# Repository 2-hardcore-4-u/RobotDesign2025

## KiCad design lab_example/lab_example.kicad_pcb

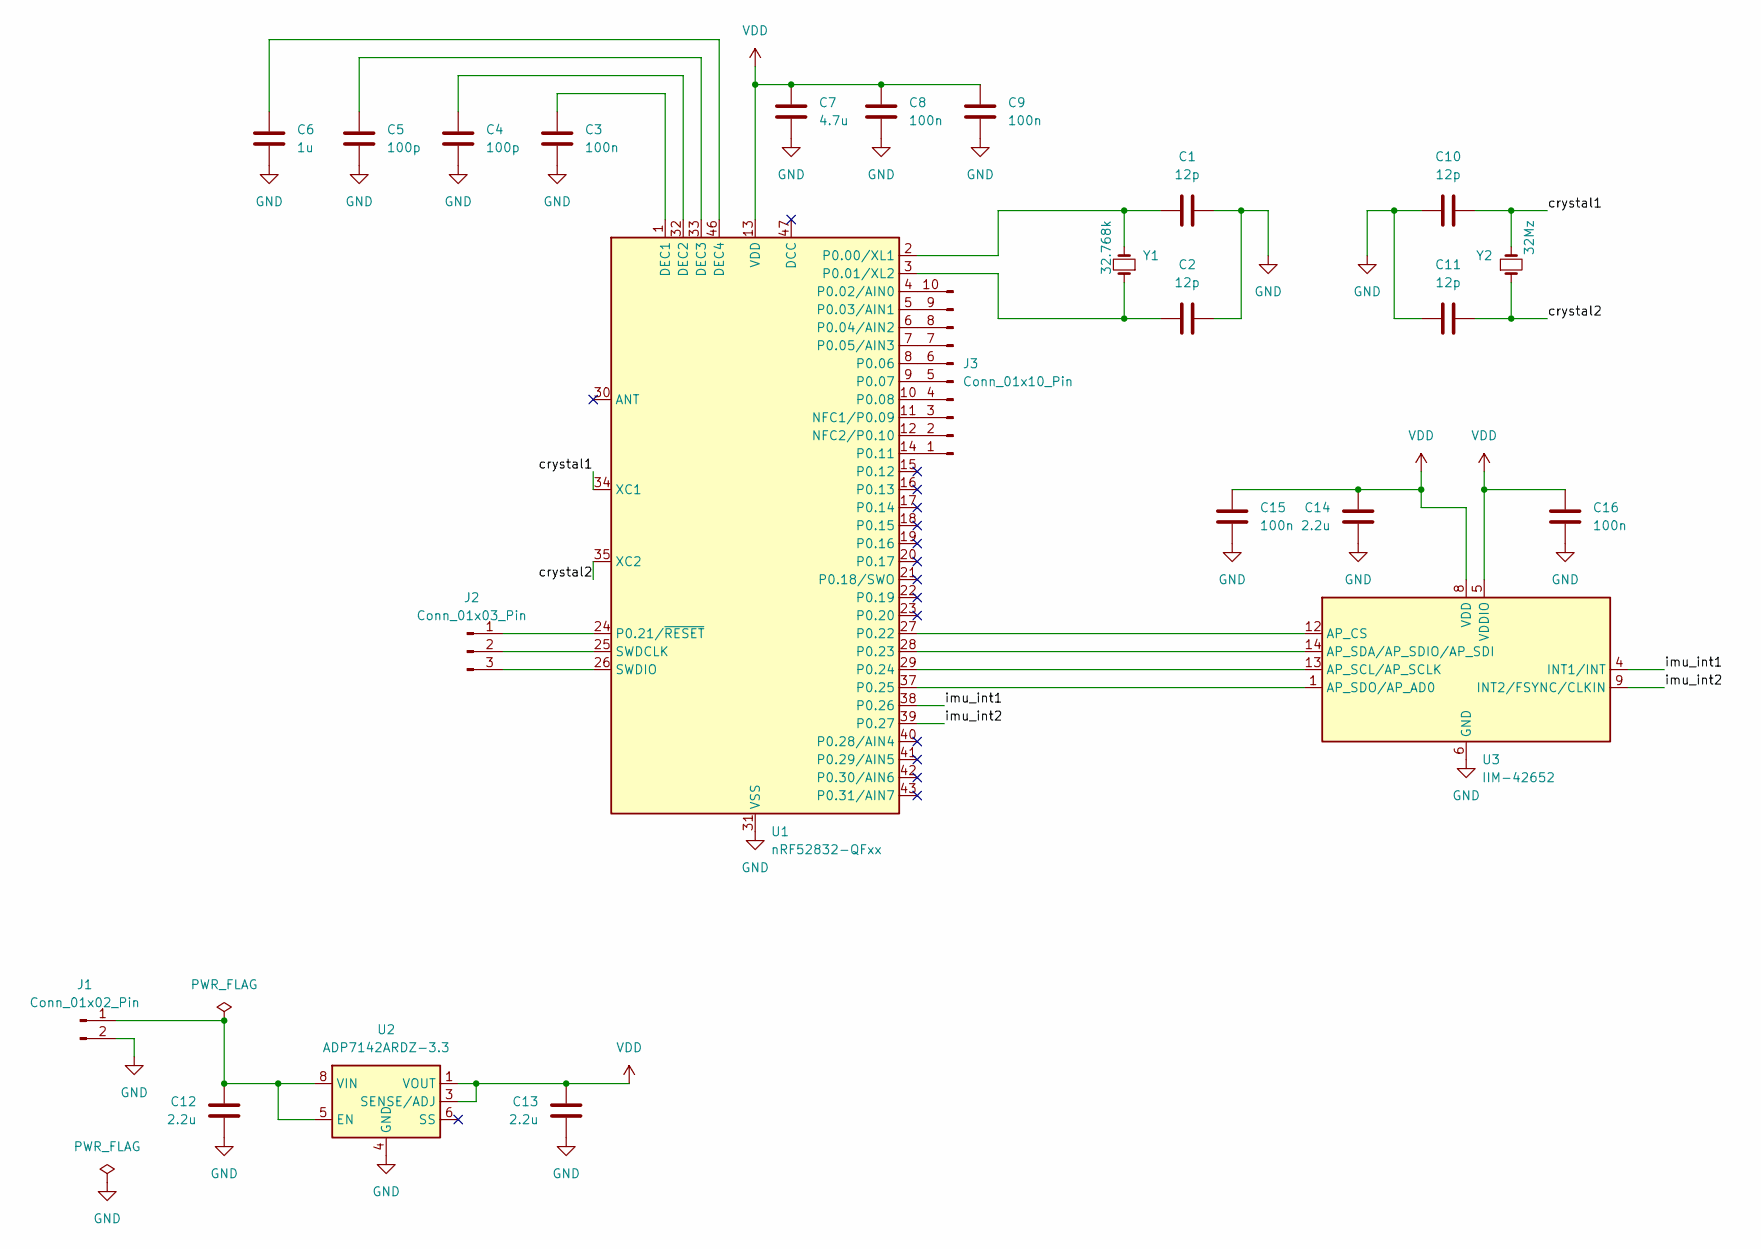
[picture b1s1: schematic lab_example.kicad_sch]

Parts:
C1, C2, C10, C11: 12p; C_0805_2012Metric
C3, C8, C9, C15, C16: 100n; C_0805_2012Metric
C4, C5: 100p; C_0805_2012Metric
C6: 1u; C_0805_2012Metric
C7: 4.7u; C_0805_2012Metric
C12, C13, C14: 2.2u; C_0805_2012Metric
J1: Conn_01x02_Pin; PinHeader_1x02_P2.54mm_Horizontal
J2: Conn_01x03_Pin; PinHeader_1x03_P2.54mm_Horizontal
J3: Conn_01x10_Pin; PinHeader_1x10_P2.54mm_Vertical
U1: nRF52832-QFxx; QFN-48-1EP_6x6mm_P0.4mm_EP4.6x4.6mm
U2: ADP7142ARDZ-3.3; SOIC-8-1EP_3.9x4.9mm_P1.27mm_EP2.29x3mm
U3: IIM-42652; Bosch_LGA-14_3x2.5mm_P0.5mm
Y1: 32.768k; Crystal_SMD_2012-2Pin_2.0x1.2mm_HandSoldering
Y2: 32Mz; Crystal_SMD_2012-2Pin_2.0x1.2mm_HandSoldering

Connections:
/crystal1: C10.1, U1.34 (XC1), Y2.2
/crystal2: C11.2, U1.35 (XC2), Y2.1
/imu_int1: U1.38 (P0.26), U3.4 (INT1/INT)
/imu_int2: U1.39 (P0.27), U3.9 (INT2/FSYNC/CLKIN)
GND: C1.2, C2.1, C3.2, C4.2, C5.2, C6.2, C7.2, C8.2, C9.2, C10.2, C11.1, C12.1, C13.1, C14.1, C15.2, C16.2, J1.2, U1.31 (VSS), U1.45 (VSS), U1.49 (VSS), U2.4 (GND), U2.9 (GND), U3.6 (GND), U3.7 (GND)
unnamed: C12.2, J1.1, U2.5 (EN), U2.7 (VIN), U2.8 (VIN)
unnamed: J2.1, U1.24 (P0.21/~RESET)
unnamed: J2.2, U1.25 (SWDCLK)
unnamed: J2.3, U1.26 (SWDIO)
unnamed: J3.1, U1.14 (P0.11)
unnamed: J3.2, U1.12 (NFC2/P0.10)
unnamed: J3.3, U1.11 (NFC1/P0.09)
unnamed: J3.4, U1.10 (P0.08)
unnamed: J3.5, U1.9 (P0.07)
unnamed: J3.6, U1.8 (P0.06)
unnamed: J3.7, U1.7 (P0.05/AIN3)
unnamed: J3.8, U1.6 (P0.04/AIN2)
unnamed: J3.9, U1.5 (P0.03/AIN1)
unnamed: J3.10, U1.4 (P0.02/AIN0)
unnamed: C3.1, U1.1 (DEC1)
unnamed: C4.1, U1.32 (DEC2)
unnamed: C5.1, U1.33 (DEC3)
unnamed: C6.1, U1.46 (DEC4)
unnamed: C1.1, U1.2 (P0.00/XL1), Y1.2
unnamed: C2.2, U1.3 (P0.01/XL2), Y1.1
unnamed: U1.27 (P0.22), U3.12 (AP_CS)
unnamed: U1.28 (P0.23), U3.14 (AP_SDA/AP_SDIO/AP_SDI)
unnamed: U1.29 (P0.24), U3.13 (AP_SCL/AP_SCLK)
unnamed: U1.37 (P0.25), U3.1 (AP_SDO/AP_AD0)
VDD: C7.1, C8.1, C9.1, C13.2, C14.2, C15.1, C16.1, U1.13 (VDD), U1.36 (VDD), U1.48 (VDD), U2.1 (VOUT), U2.2 (VOUT), U2.3 (SENSE/ADJ), U3.5 (VDDIO), U3.8 (VDD)

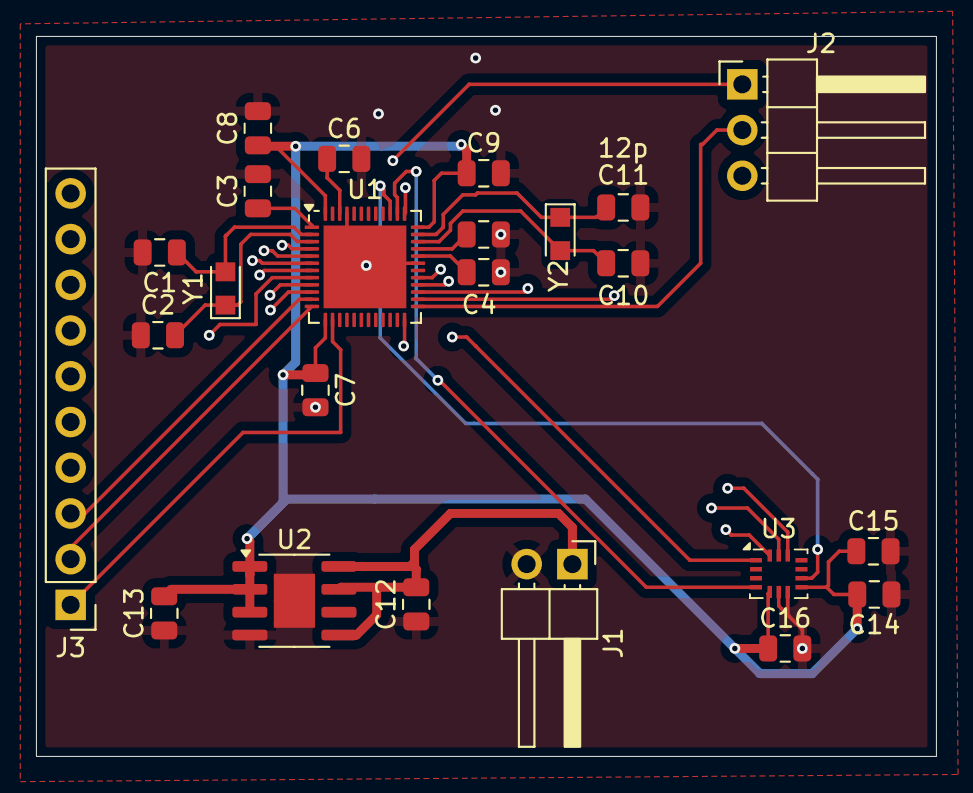
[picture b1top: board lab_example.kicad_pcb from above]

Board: 4 copper layers, 50.0 x 40.0 mm, 24 parts (0 on the bottom side), 30 nets.

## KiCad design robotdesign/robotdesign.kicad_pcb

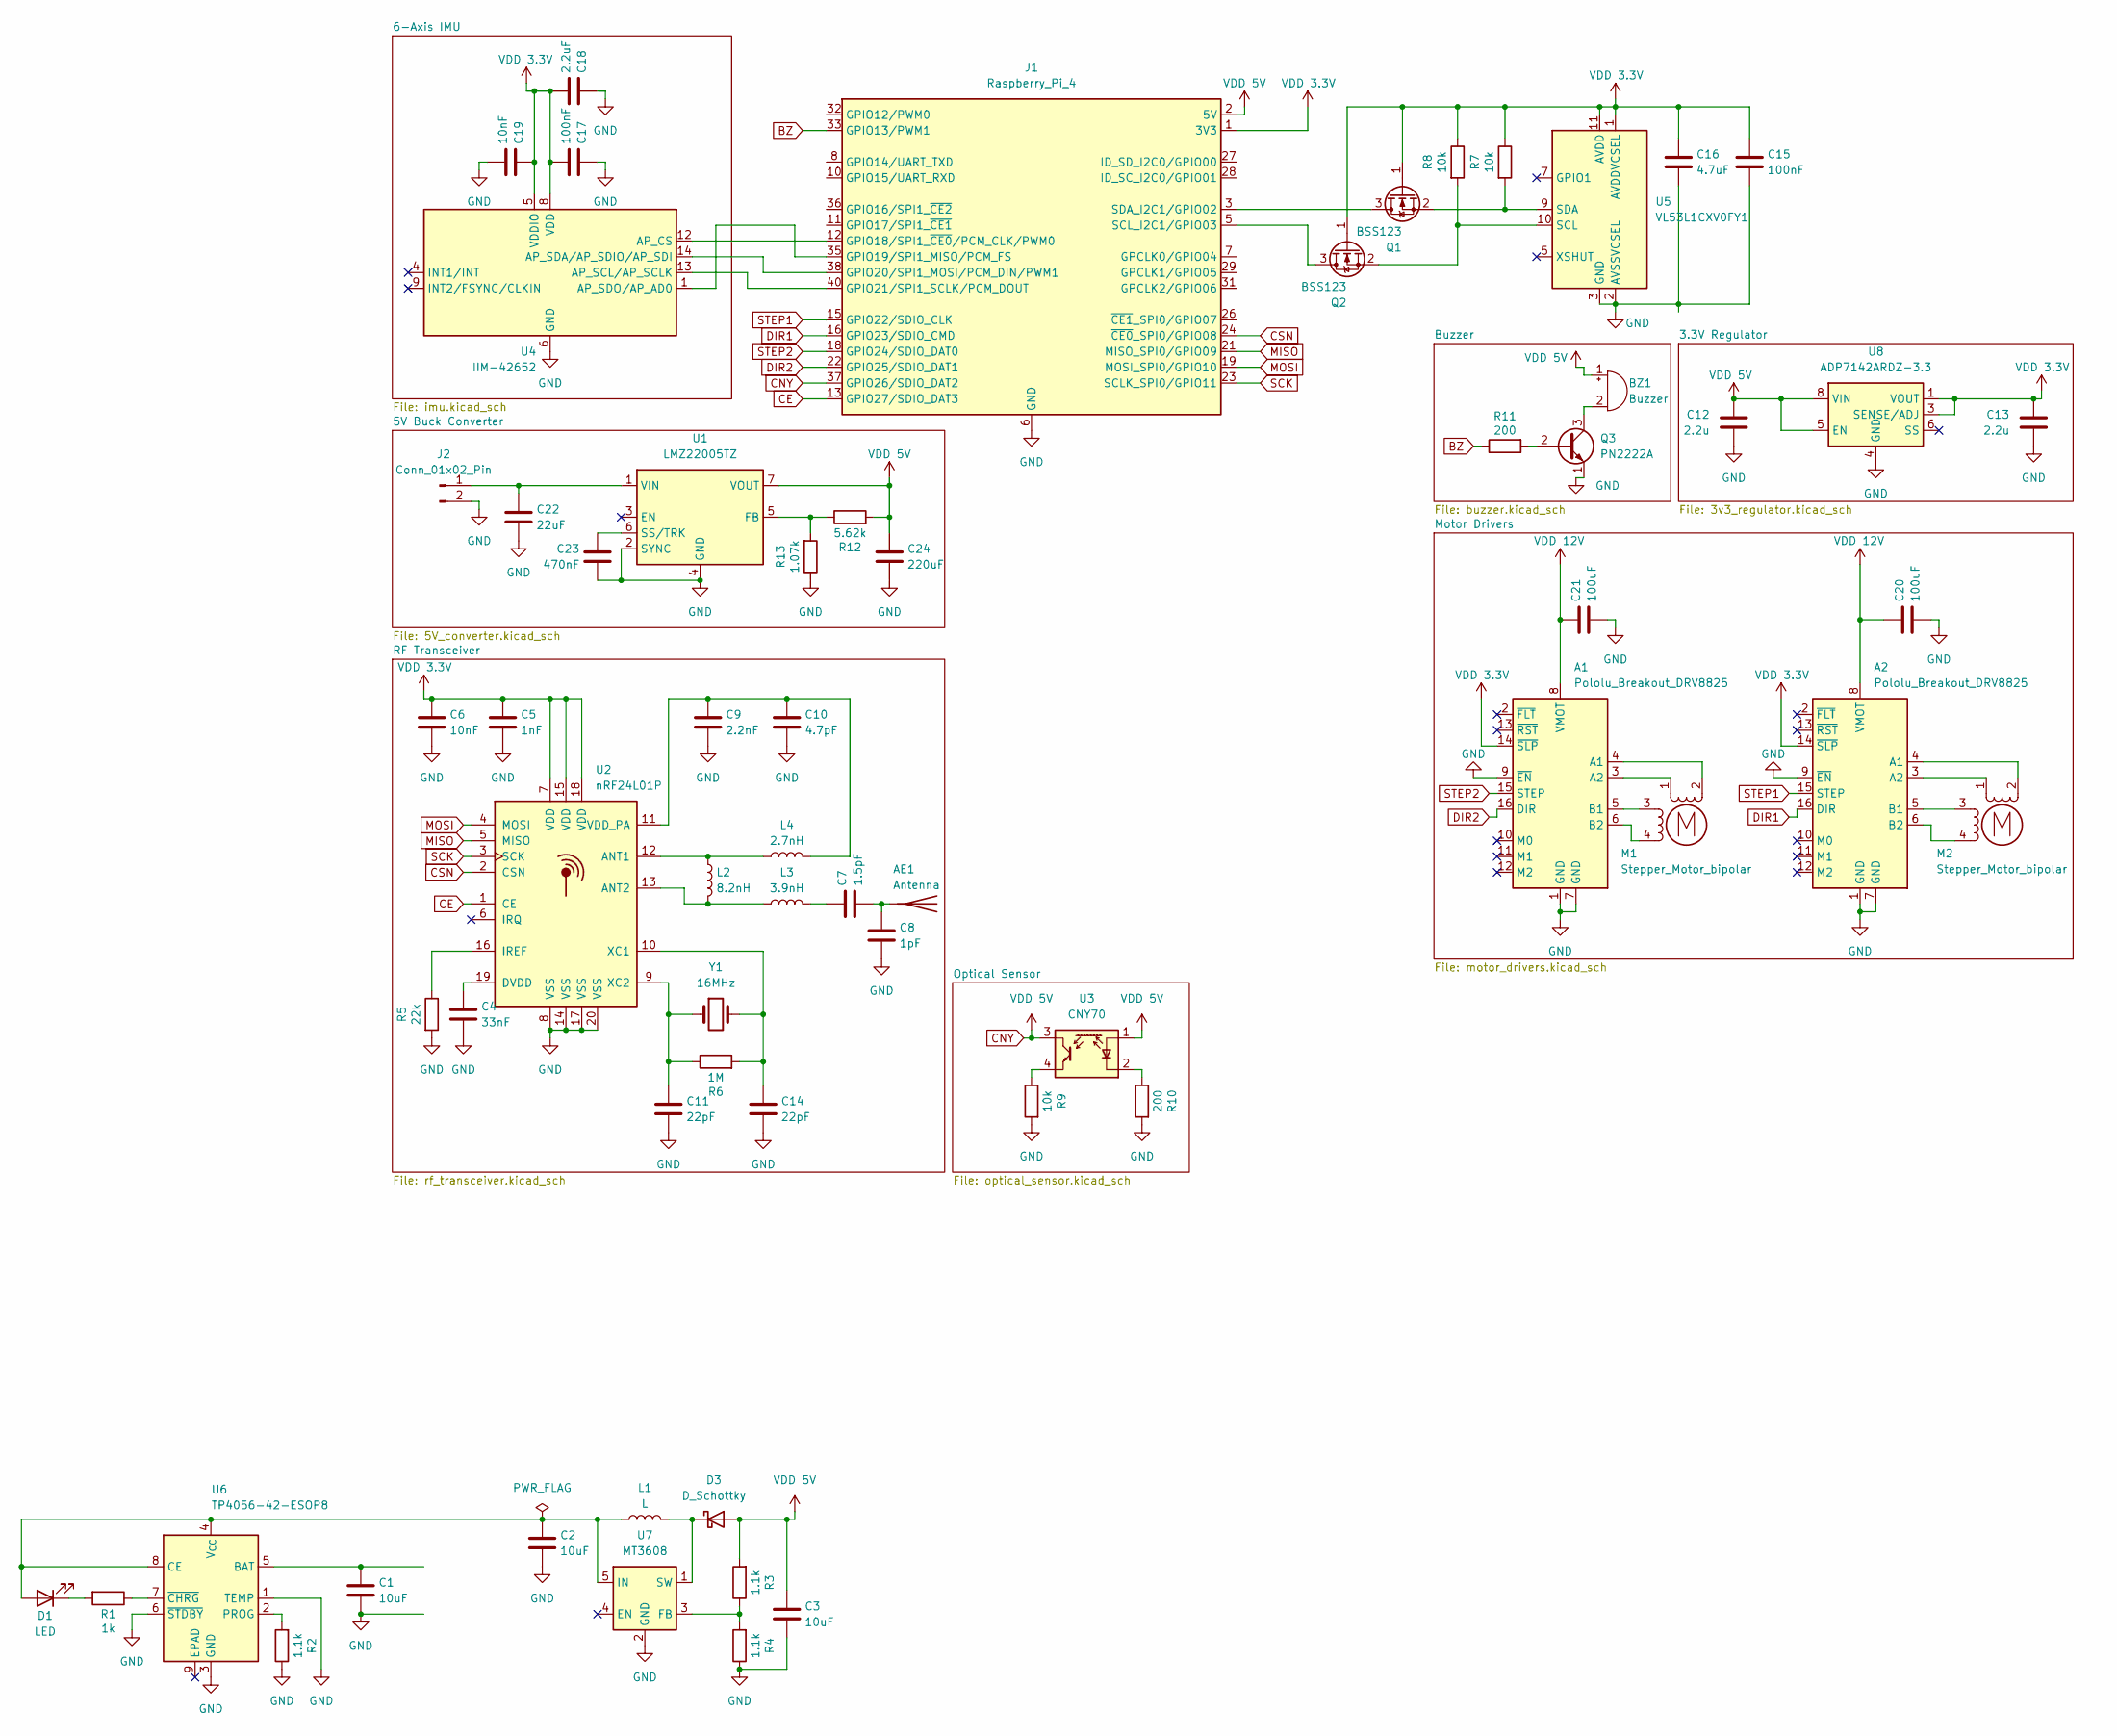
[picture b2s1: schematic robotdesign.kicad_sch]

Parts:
A1, A2: Pololu_Breakout_DRV8825; Pololu_Breakout-16_15.2x20.3mm
AE1: Antenna; NiceRF_SW868-TH13_868Mhz
BZ1: Buzzer; Buzzer_12x9.5RM7.6
C1, C2, C3: 10uF; C_0201_0603Metric
C4: 33nF; C_0201_0603Metric
C5: 1nF; C_0201_0603Metric
C6, C19: 10nF; C_0201_0603Metric
C7: 1.5pF; C_0201_0603Metric
C8: 1pF; C_0201_0603Metric
C9: 2.2nF; C_0201_0603Metric
C10: 4.7pF; C_0201_0603Metric
C11, C14: 22pF; C_0201_0603Metric
C12, C13: 2.2u; C_0805_2012Metric
C15, C17: 100nF; C_0201_0603Metric
C16: 4.7uF; C_0201_0603Metric
C18: 2.2uF; C_0201_0603Metric
C20, C21: 100uF; C_0201_0603Metric
C22: 22uF; C_0201_0603Metric
C23: 470nF; C_0201_0603Metric
C24: 220uF; C_0201_0603Metric
D1: LED; LED_0201_0603Metric
D3: D_Schottky; D_0201_0603Metric
J1: Raspberry_Pi_4; PinHeader_2x20_P2.54mm_Vertical
J2: Conn_01x02_Pin; JWT_A3963_1x02_P3.96mm_Vertical
L1: L; L_6.3x6.3_H3
L2: 8.2nH; L_6.3x6.3_H3
L3: 3.9nH; L_6.3x6.3_H3
L4: 2.7nH; L_6.3x6.3_H3
M1, M2: Stepper_Motor_bipolar; PinHeader_1x04_P2.54mm_Vertical
Q1, Q2: BSS123; SOT-23
Q3: PN2222A; TO-92_Inline
R1: 1k; R_0201_0603Metric
R2, R3, R4: 1.1k; R_0201_0603Metric
R5: 22k; R_0201_0603Metric
R6: 1M; R_0201_0603Metric
R7, R8, R9: 10k; R_0201_0603Metric
R10, R11: 200; R_0201_0603Metric
R12: 5.62k; R_0201_0603Metric
R13: 1.07k; R_0201_0603Metric
U1: LMZ22005TZ; Texas_NDW-7_TabPin4
U2: nRF24L01P; QFN-20-1EP_4x4mm_P0.5mm_EP2.5x2.5mm
U3: CNY70; Vishay_CNY70
U4: IIM-42652; Bosch_LGA-14_3x2.5mm_P0.5mm
U5: VL53L1CXV0FY1; ST_VL53L1x
U6: TP4056-42-ESOP8; SOIC-8-1EP_3.9x4.9mm_P1.27mm_EP2.41x3.3mm_ThermalVias
U7: MT3608; SOT-23-6
U8: ADP7142ARDZ-3.3; SOIC-8-1EP_3.9x4.9mm_P1.27mm_EP2.29x3mm
Y1: 16MHz; Crystal_AT310_D3.0mm_L10.0mm_Horizontal

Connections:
BZ: J1.33 (GPIO13/PWM1), R11.1
CE: J1.13 (GPIO27/SDIO_DAT3), U2.1 (CE)
CNY: BZ1.1 (+), C3.1, C12.2, C24.1, D3.2 (A), J1.2 (5V), J1.4 (5V), J1.37 (GPIO26/SDIO_DAT2), R3.2, R12.2, U1.7 (VOUT), U3.1 (A), U3.3 (C), U8.5 (EN), U8.7 (VIN), U8.8 (VIN)
CSN: J1.24 (~CE0_SPI0/GPIO08), U2.2 (CSN)
DIR1: A2.16 (DIR), J1.16 (GPIO23/SDIO_CMD)
DIR2: A1.16 (DIR), J1.22 (GPIO25/SDIO_DAT1)
GND: A1.1 (GND), A1.7 (GND), A1.9 (~EN), A2.1 (GND), A2.7 (GND), A2.9 (~EN), C1.2, C2.2, C3.2, C4.2, C5.2, C6.2, C8.2, C9.2, C10.2, C11.2, C12.1, C13.1, C14.2, C15.2, C16.2, C17.1, C18.1, C19.2, C20.2, C21.2, C22.2, C23.2, C24.2, J1.6 (GND), J1.9 (GND), J1.14 (GND), J1.20 (GND), J1.25 (GND), J1.30 (GND), J1.34 (GND), J1.39 (GND), J2.2, Q3.1 (E), R2.1, R4.1, R5.2, R9.2, R10.2, R13.1, U1.2 (SYNC), U1.4 (GND), U2.8 (VSS), U2.14 (VSS), U2.17 (VSS), U2.20 (VSS), U4.6 (GND), U4.7 (GND), U5.2 (AVSSVCSEL), U5.3 (GND), U5.4 (GND), U5.6 (GND), U5.12 (GND), U6.1 (TEMP), U6.3 (GND), U6.6 (~STDBY), U7.2 (GND), U8.4 (GND), U8.9 (GND); also elsewhere on the board
MISO: J1.21 (MISO_SPI0/GPIO09), U2.5 (MISO)
MOSI: J1.19 (MOSI_SPI0/GPIO10), U2.4 (MOSI)
unnamed: A1.4 (A1), M1.2 (-)
unnamed: A1.3 (A2), M1.1
unnamed: A1.5 (B1), M1.3
unnamed: A1.6 (B2), M1.4
unnamed: A2.4 (A1), M2.2 (-)
unnamed: A2.3 (A2), M2.1
unnamed: A2.5 (B1), M2.3
unnamed: A2.6 (B2), M2.4
unnamed: AE1.1 (A), C7.2, C8.1
unnamed: BZ1.2 (-), Q3.3 (C)
unnamed: C7.1, L3.2
unnamed: C2.1, D1.2 (A), L1.1, U6.4 (V_{CC}), U6.8 (CE), U7.5 (IN)
unnamed: D1.1 (K), R1.2
unnamed: D3.1 (K), L1.2, U7.1 (SW)
unnamed: J1.12 (GPIO18/SPI1_~CE0/PCM_CLK/PWM0), U4.12 (AP_CS)
unnamed: J1.35 (GPIO19/SPI1_MISO/PCM_FS), U4.1 (AP_SDO/AP_AD0)
unnamed: J1.38 (GPIO20/SPI1_MOSI/PCM_DIN/PWM1), U4.14 (AP_SDA/AP_SDIO/AP_SDI)
unnamed: J1.40 (GPIO21/SPI1_SCLK/PCM_DOUT), U4.13 (AP_SCL/AP_SCLK)
unnamed: J1.5 (SCL_I2C1/GPIO03), Q2.3 (D)
unnamed: J1.3 (SDA_I2C1/GPIO02), Q1.3 (D)
unnamed: C22.1, J2.1, U1.1 (VIN)
unnamed: Q1.2 (S), R7.2, U5.9 (SDA)
unnamed: Q2.2 (S), R8.2, U5.10 (SCL)
unnamed: Q3.2 (B), R11.2
unnamed: R12.1, R13.2, U1.5 (FB)
unnamed: C23.1, U1.6 (SS/TRK)
unnamed: L2.1, L4.1, U2.12 (ANT1)
unnamed: L2.2, L3.1, U2.13 (ANT2)
unnamed: C4.1, U2.19 (DVDD)
unnamed: R5.1, U2.16 (IREF)
unnamed: C9.1, C10.1, L4.2, U2.11 (VDD_PA)
unnamed: C14.1, R6.2, U2.10 (XC1), Y1.2
unnamed: C11.1, R6.1, U2.9 (XC2), Y1.1
unnamed: R9.1, U3.4 (E)
unnamed: R10.1, U3.2 (K)
unnamed: C1.1, U6.5 (BAT)
unnamed: R2.2, U6.2 (PROG)
unnamed: R1.1, U6.7 (~CHRG)
unnamed: R3.1, R4.2, U7.3 (FB)
SCK: J1.23 (SCLK_SPI0/GPIO11), U2.3 (SCK)
STEP1: A2.15 (STEP), J1.15 (GPIO22/SDIO_CLK)
STEP2: A1.15 (STEP), J1.18 (GPIO24/SDIO_DAT0)
VDD 3.3V: A1.14 (~SLP), A2.14 (~SLP), C5.1, C6.1, C13.2, C15.1, C16.1, C17.2, C18.2, C19.1, J1.1 (3V3), J1.17 (3V3), Q1.1 (G), Q2.1 (G), R7.1, R8.1, U2.7 (VDD), U2.15 (VDD), U2.18 (VDD), U4.5 (VDDIO), U4.8 (VDD), U5.1 (AVDDVCSEL), U5.11 (AVDD), U8.1 (VOUT), U8.2 (VOUT), U8.3 (SENSE/ADJ)
VDD 12V: A1.8 (VMOT), A2.8 (VMOT), C20.1, C21.1

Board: 2 copper layers, 64 parts (0 on the bottom side), 53 nets, no tracks yet.

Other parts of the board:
BT1: Battery_Cell; PinHeader_1x02_P2.54mm_Horizontal

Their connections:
GND: BT1.2 (-); also elsewhere on the board

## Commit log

2025-06-22 circuit v1
2025-07-10 bill of materials and report
2025-07-10 presentation
2025-07-11 final commit
